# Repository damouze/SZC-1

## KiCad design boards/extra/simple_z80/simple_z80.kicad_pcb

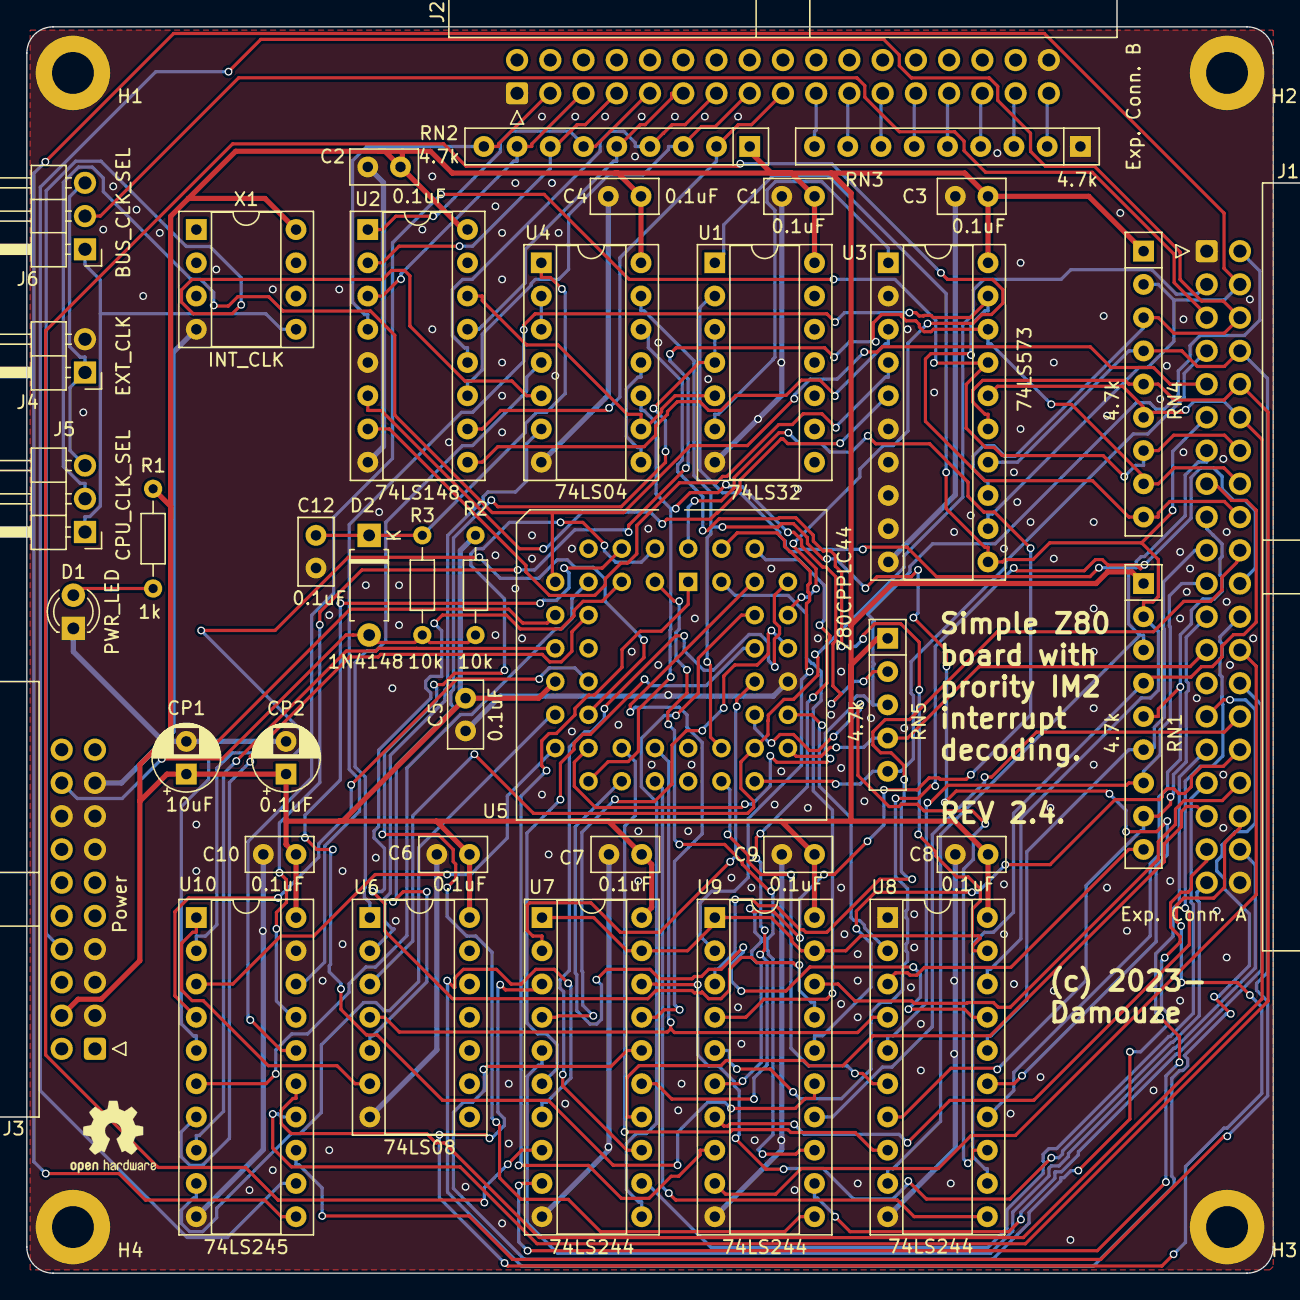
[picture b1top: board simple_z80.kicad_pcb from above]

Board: 2 copper layers, 95.2 x 95.2 mm, 44 parts (0 on the bottom side), 107 nets.

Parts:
C1, C2, C3, C4, C5, C6, C7, C8, C9, C10, C12: 0.1uF; C_Disc_D5.0mm_W2.5mm_P2.50mm
CP1: 10uF; CP_Radial_D5.0mm_P2.50mm
CP2: 0.1uF; CP_Radial_D5.0mm_P2.50mm
D1: PWR_LED; LED_D3.0mm
D2: 1N4148; D_A-405_P7.62mm_Horizontal
H1, H2, H3, H4: MountingHole_Pad; MountingHole_3.2mm_M3_ISO7380_Pad
J1: Exp. Conn. A; IDC-Header_2x20_P2.54mm_Horizontal
J2: Exp. Conn. B; IDC-Header_2x17_P2.54mm_Horizontal
J3: Power; IDC-Header_2x10_P2.54mm_Horizontal
J4: EXT_CLK; PinHeader_1x02_P2.54mm_Horizontal
J5: CPU_CLK_SEL; PinHeader_1x03_P2.54mm_Horizontal
J6: BUS_CLK_SEL; PinHeader_1x03_P2.54mm_Horizontal
R1: 1k; R_Axial_DIN0204_L3.6mm_D1.6mm_P7.62mm_Horizontal
R2, R3: 10k; R_Axial_DIN0204_L3.6mm_D1.6mm_P7.62mm_Horizontal
RN1, RN2, RN3, RN4: 4.7k; R_Array_SIP9
RN5: 4.7k; R_Array_SIP5
U1: 74LS32; DIP-14_W7.62mm_Socket
U2: 74LS148; DIP-16_W7.62mm_Socket
U3: 74LS573; DIP-20_W7.62mm_Socket
U4: 74LS04; DIP-14_W7.62mm_Socket
U5: Z80CPPLC44; PLCC-44_THT-Socket
U6: 74LS08; DIP-14_W7.62mm_Socket
U7, U8, U9: 74LS244; DIP-20_W7.62mm_Socket
U10: 74LS245; DIP-20_W7.62mm_Socket
X1: INT_CLK; DIP-8_W7.62mm_Socket

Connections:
/+5V: C1.1, C2.2, C3.1, C4.1, C5.1, C6.1, C7.1, C8.1, C9.1, C10.1, CP1.1, CP2.1, J3.4, R1.1, R2.1, RN1.1 (common), RN2.1 (common), RN4.1 (common), RN5.1 (common), U1.14 (VCC), U2.16 (VCC), U3.20 (VCC), U4.14 (VCC), U5.13 (VCC), U6.14 (VCC), U7.20 (VCC), U8.20 (VCC), U9.20 (VCC), U10.20 (VCC), X1.8 (Vcc)
/BUS_CLK: J1.5, J6.2
/B_A0: J1.39, U7.18 (O0a)
/B_A1: J1.37, U7.16 (O1a)
/B_A2: J1.35, U7.14 (O2a)
/B_A3: J1.33, U7.12 (O3a)
/B_A4: J1.31, U7.9 (O0b)
/B_A5: J1.29, U7.7 (O1b)
/B_A6: J1.38, U7.5 (O2b)
/B_A7: J1.36, U7.3 (O3b)
/B_A8: J1.34, U9.18 (O0a)
/B_A9: J1.32, U9.16 (O1a)
/B_A10: J1.30, U9.14 (O2a)
/B_A11: J1.28, U9.12 (O3a)
/B_A12: J1.26, U9.9 (O0b)
/B_A13: J1.24, U9.7 (O1b)
/B_A14: J1.22, U9.5 (O2b)
/B_A15: J1.20, U9.3 (O3b)
/B_D0: J1.18, RN4.9 (R8), U3.19 (Q0), U10.18 (B0)
/B_D1: J1.16, RN4.8 (R7), U3.18 (Q1), U10.17 (B1)
/B_D2: J1.14, RN4.7 (R6), U3.17 (Q2), U10.16 (B2)
/B_D3: J1.12, RN4.6 (R5), U3.16 (Q3), U10.15 (B3)
/B_D4: J1.10, RN4.5 (R4), U3.15 (Q4), U10.14 (B4)
/B_D5: J1.8, RN4.4 (R3), U3.14 (Q5), U10.13 (B5)
/B_D6: J1.6, RN4.3 (R2), U3.13 (Q6), U10.12 (B6)
/B_D7: J1.4, RN4.2 (R1), U3.12 (Q7), U10.11 (B7)
/CPU_CLK: J1.9, J5.2, U5.7 (~CLK)
/Clock & Reset circuit/EXT_CLK: J4.1, J5.3, J6.3
/Clock & Reset circuit/INT_CLK: J5.1, J6.1, X1.5 (OUT)
/Clock & Reset circuit/RESET1: U4.2, U4.3
/Clock & Reset circuit/~PWR_OK: U4.6, U6.2
/Clock & Reset circuit/~RESET1: U4.4, U6.1
/GND: C1.2, C2.1, C3.2, C4.2, C5.2, C6.2, C7.2, C8.2, C9.2, C10.2, C12.2, CP1.2, CP2.2, D1.1 (K), H1.1, H2.1, H3.1, H4.1, J1.1, J1.40, J2.1, J2.34, J3.3, J3.5, J3.7, J3.13, J3.15, J3.16, J3.17, J4.2, RN3.1 (common), U1.7 (GND), U2.5 (EI), U2.8 (GND), U3.2 (D0), U3.6 (D4), U3.7 (D5), U3.8 (D6), U3.9 (D7), U3.10 (GND), U4.7 (GND), U5.33 (GND), U6.7 (GND), U7.10 (GND), U8.1 (OEa), U8.10 (GND), U9.10 (GND), U10.10 (GND), U10.19 (CE), X1.4 (GND)
/MCU/A0: U5.34 (A0), U7.2 (I0a)
/MCU/A1: U5.35 (A1), U7.4 (I1a)
/MCU/A2: U5.36 (A2), U7.6 (I2a)
/MCU/A3: U5.37 (A3), U7.8 (I3a)
/MCU/A4: U5.38 (A4), U7.11 (I0b)
/MCU/A5: U5.39 (A5), U7.13 (I1b)
/MCU/A6: U5.40 (A6), U7.15 (I2b)
/MCU/A7: U5.41 (A7), U7.17 (I3b)
/MCU/A8: U5.42 (A8), U9.2 (I0a)
/MCU/A9: U5.43 (A9), U9.4 (I1a)
/MCU/A10: U5.44 (A10), U9.6 (I2a)
/MCU/A11: U5.1 (A11), U9.8 (I3a)
/MCU/A12: U5.2 (A12), U9.11 (I0b)
/MCU/A13: U5.3 (A13), U9.13 (I1b)
/MCU/A14: U5.4 (A14), U9.15 (I2b)
/MCU/A15: U5.5 (A15), U9.17 (I3b)
/MCU/BUSACK: U4.12, U7.1 (OEa), U7.19 (OEb), U8.19 (OEb), U9.1 (OEa), U9.19 (OEb)
/MCU/D0: U5.16 (D0), U10.2 (A0)
/MCU/D1: U5.17 (D1), U10.3 (A1)
/MCU/D2: U5.14 (D2), U10.4 (A2)
/MCU/D3: U5.9 (D3), U10.5 (A3)
/MCU/D4: U5.8 (D4), U10.6 (A4)
/MCU/D5: U5.10 (D5), U10.7 (A5)
/MCU/D6: U5.11 (D6), U10.8 (A6)
/MCU/D7: U5.15 (D7), U10.9 (A7)
/MCU/~BUSACK: U4.13, U5.27 (~BUSACK), U8.15 (I2b)
/MCU/~HALT: U5.20 (~HALT), U8.17 (I3b)
/MCU/~IORQ: U5.22 (~IORQ), U8.11 (I0b)
/MCU/~M1: U5.31 (~M1), U8.2 (I0a)
/MCU/~MREQ: U5.21 (~MREQ), U8.8 (I3a)
/MCU/~RD: U5.23 (~RD), U6.4, U8.4 (I1a)
/MCU/~RFSH: U5.32 (~RFSH), U8.13 (I1b)
/MCU/~WR: U5.26 (~WR), U8.6 (I2a)
/M_A14: J2.33, RN3.2 (R1)
/M_A15: J2.31, RN3.3 (R2)
/M_A16: J2.29, RN3.4 (R3)
/M_A17: J2.27, RN3.5 (R4)
/M_A18: J2.25, RN3.6 (R5)
/M_A19: J2.23, RN3.7 (R6)
/M_A20: J2.21, RN3.8 (R7)
/M_A21: J2.19, RN3.9 (R8)
/PWR_OK: J3.8, U4.5
/~BUSREQ: J1.25, RN5.4 (R3), U5.29 (~BUSRQ)
/~B_BUSACK: J1.21, RN1.7 (R6), U8.5 (O2b)
/~B_HALT: RN1.9 (R8), U8.3 (O3b)
/~B_IORQ: J1.13, RN1.3 (R2), U1.2, U8.9 (O0b)
/~B_M1: J1.11, RN1.2 (R1), U1.1, U3.11 (Load), U8.18 (O0a)
/~B_MREQ: J1.15, RN1.4 (R3), U8.12 (O3a)
/~B_RD: J1.19, RN1.6 (R5), U8.16 (O1a)
/~B_RFSH: J1.23, RN1.8 (R7), U8.7 (O1b)
/~B_WR: J1.17, RN1.5 (R4), U8.14 (O2a)
/~CPU_INT: RN5.2 (R1), U4.10, U5.18 (~INT)
/~IM2_INT: U1.5, U2.14 (GS), U4.9
/~INT0: J2.17, RN2.2 (R1), U2.10 (IO)
/~INT1: J2.15, RN2.3 (R2), U2.11 (I1)
/~INT2: J2.13, RN2.4 (R3), U2.12 (I2)
/~INT3: J2.11, RN2.5 (R4), U2.13 (I3)
/~INT4: J2.9, RN2.6 (R5), U2.1 (I4)
/~INT5: J2.7, RN2.7 (R6), U2.2 (I5)
/~INT6: J2.5, RN2.8 (R7), U2.3 (I6)
/~INT7: J2.3, RN2.9 (R8), U2.4 (I7)
/~INTA: U1.3, U1.4, U6.5
/~NMI: J1.2, RN5.3 (R2), U5.19 (~NMI)
/~RESET_SW: D2.2 (A), J3.18, R2.2, R3.2
/~RESET: J1.3, U5.30 (~RESET), U6.3
/~WAIT: J1.7, RN5.5 (R4), U5.28 (~WAIT)
unnamed: D1.2 (A), R1.2
unnamed: C12.1, D2.1 (K), R3.1, U4.1
unnamed: U2.9 (S0), U3.3 (D1)
unnamed: U2.7 (S1), U3.4 (D2)
unnamed: U2.6 (S2), U3.5 (D3)
unnamed: U1.6, U3.1 (OE)
unnamed: U4.8, U4.11
unnamed: U6.6, U10.1 (A->B)

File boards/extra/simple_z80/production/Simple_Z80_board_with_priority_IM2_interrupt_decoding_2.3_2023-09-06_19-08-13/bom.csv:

Designator,Footprint,Quantity,Value,LCSC Part #
"C1, C10, C12, C2, C3, C4, C5, C6, C7, C8, C9",C_Disc_D5.0mm_W2.5mm_P2.50mm,11,0.1uF,
CP1,CP_Radial_D5.0mm_P2.50mm,1,10uF,
CP2,CP_Radial_D5.0mm_P2.50mm,1,0.1uF,
D1,LED_D3.0mm,1,PWR_LED,
D2,D_A-405_P7.62mm_Horizontal,1,D,
"H1, H2, H3, H4",MountingHole_3.2mm_M3_ISO7380_Pad,4,MountingHole_Pad,
J1,IDC-Header_2x20_P2.54mm_Horizontal,1,Exp. Conn. A,
J2,IDC-Header_2x17_P2.54mm_Horizontal,1,Exp. Conn. B,
J3,IDC-Header_2x10_P2.54mm_Horizontal,1,Power,
J4,PinHeader_1x02_P2.54mm_Horizontal,1,EXT_CLK,
J5,PinHeader_1x03_P2.54mm_Horizontal,1,CPU_CLK_SEL,
J6,PinHeader_1x03_P2.54mm_Horizontal,1,BUS_CLK_SEL,
R1,R_Axial_DIN0204_L3.6mm_D1.6mm_P7.62mm_Horizontal,1,470,
"R2, R3",R_Axial_DIN0204_L3.6mm_D1.6mm_P7.62mm_Horizontal,2,10k,
"RN1, RN2, RN3, RN4",R_Array_SIP9,4,4.7k,
RN5,R_Array_SIP5,1,4.7k,
U1,DIP-14_W7.62mm_Socket,1,74LS32,
U10,DIP-20_W7.62mm_Socket,1,74LS245,
U2,DIP-16_W7.62mm_Socket,1,74LS148,
U3,DIP-20_W7.62mm_Socket,1,74LS573,
U4,DIP-14_W7.62mm_Socket,1,74LS04,
U5,PLCC-44_THT-Socket,1,Z80CPPLC44,
U6,DIP-14_W7.62mm_Socket,1,74LS08,
"U7, U8, U9",DIP-20_W7.62mm_Socket,3,74LS244,
X1,DIP-8_W7.62mm_Socket,1,INT_CLK,

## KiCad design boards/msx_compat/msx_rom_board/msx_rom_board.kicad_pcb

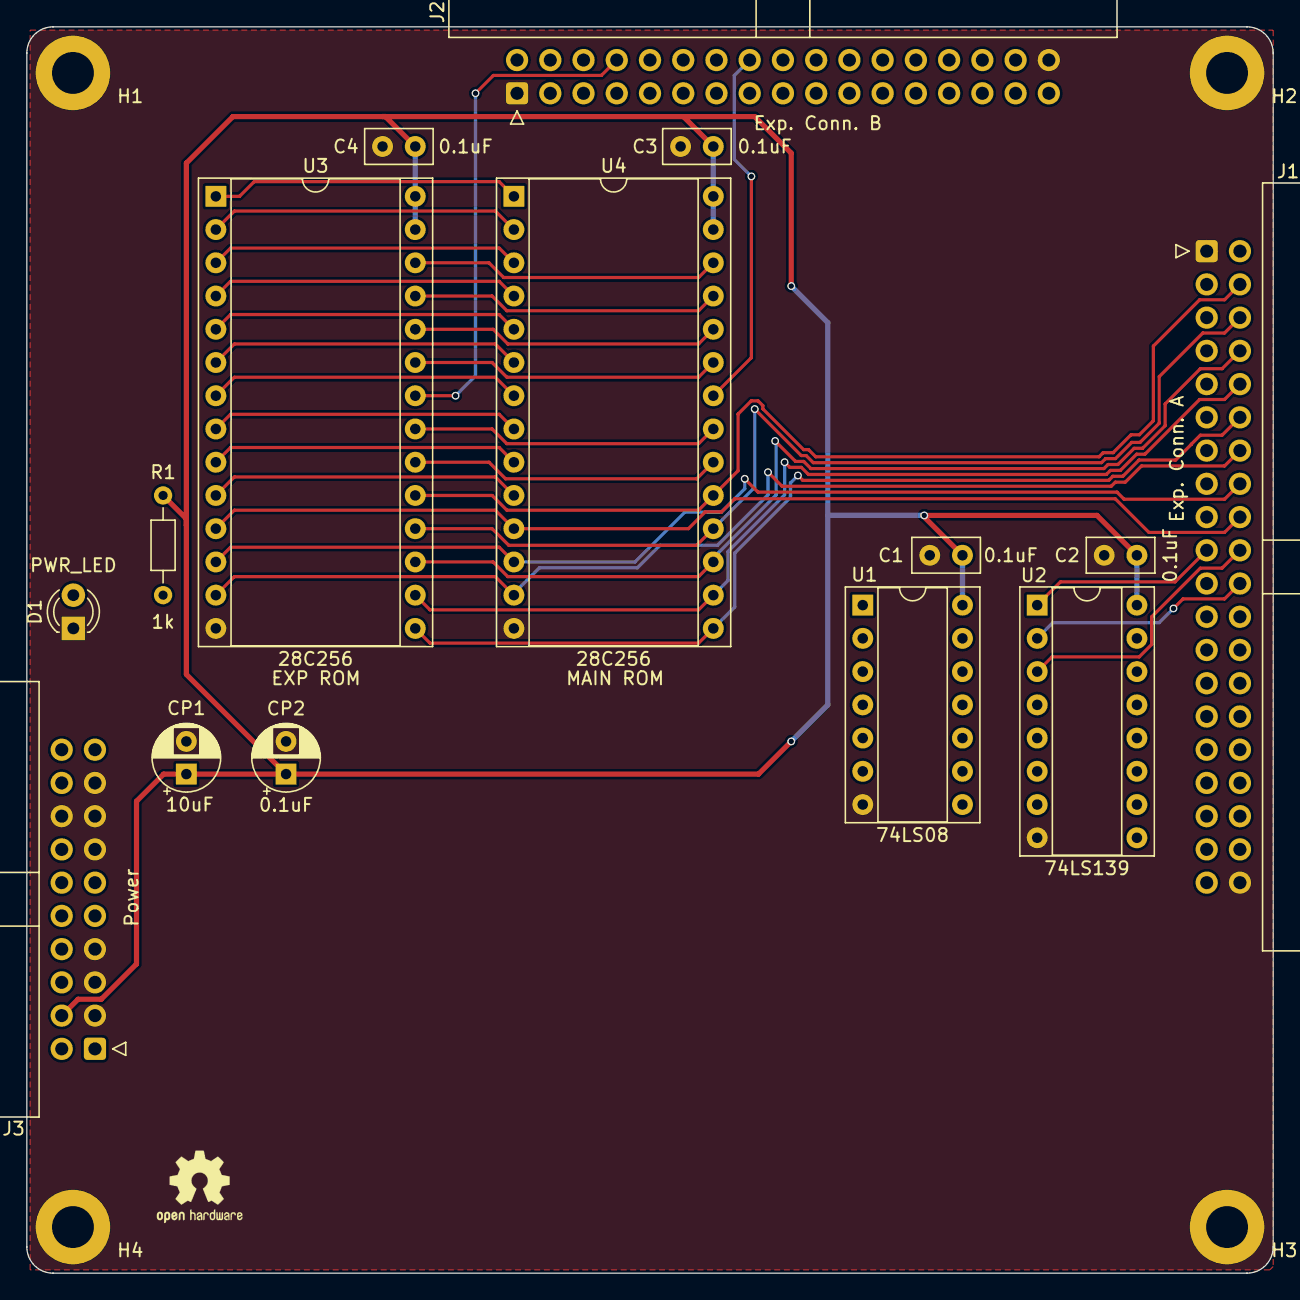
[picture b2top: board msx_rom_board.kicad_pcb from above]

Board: 2 copper layers, 95.2 x 95.2 mm, 19 parts (0 on the bottom side), 33 nets.

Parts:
C1, C2, C3, C4: 0.1uF; C_Disc_D5.0mm_W2.5mm_P2.50mm
CP1: 10uF; CP_Radial_D5.0mm_P2.50mm
CP2: 0.1uF; CP_Radial_D5.0mm_P2.50mm
D1: PWR_LED; LED_D3.0mm
H1, H2, H3, H4: MountingHole_Pad; MountingHole_3.2mm_M3_ISO7380_Pad
J1: Exp. Conn. A; IDC-Header_2x20_P2.54mm_Horizontal
J2: Exp. Conn. B; IDC-Header_2x17_P2.54mm_Horizontal
J3: Power; IDC-Header_2x10_P2.54mm_Horizontal
R1: 1k; R_Axial_DIN0204_L3.6mm_D1.6mm_P7.62mm_Horizontal
U1: 74LS08; DIP-14_W7.62mm_Socket
U2: 74LS139; DIP-16_W7.62mm_Socket
U3, U4: 28C256; DIP-28_W15.24mm_Socket

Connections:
/+5V: C1.1, C2.1, C3.1, C4.1, CP1.1, CP2.1, J3.4, R1.1, U1.14 (VCC), U2.16 (VCC), U3.27 (~WE), U3.28 (VCC), U4.27 (~WE), U4.28 (VCC)
/B_A0: J1.39, U3.10 (A0), U4.10 (A0)
/B_A1: J1.37, U3.9 (A1), U4.9 (A1)
/B_A2: J1.35, U3.8 (A2), U4.8 (A2)
/B_A3: J1.33, U3.7 (A3), U4.7 (A3)
/B_A4: J1.31, U3.6 (A4), U4.6 (A4)
/B_A5: J1.29, U3.5 (A5), U4.5 (A5)
/B_A6: J1.38, U3.4 (A6), U4.4 (A6)
/B_A7: J1.36, U3.3 (A7), U4.3 (A7)
/B_A8: J1.34, U3.25 (A8), U4.25 (A8)
/B_A9: J1.32, U3.24 (A9), U4.24 (A9)
/B_A10: J1.30, U3.21 (A10), U4.21 (A10)
/B_A11: J1.28, U3.23 (A11), U4.23 (A11)
/B_A12: J1.26, U3.2 (A12), U4.2 (A12)
/B_A13: J1.24, U3.26 (A13), U4.26 (A13)
/B_A14: J1.22, U2.2 (A0), U3.1 (A14), U4.1 (A14)
/B_A15: J1.20, U2.3 (A1)
/B_D0: J1.18, U3.11 (D0), U4.11 (D0)
/B_D1: J1.16, U3.12 (D1), U4.12 (D1)
/B_D2: J1.14, U3.13 (D2), U4.13 (D2)
/B_D3: J1.12, U3.15 (D3), U4.15 (D3)
/B_D4: J1.10, U3.16 (D4), U4.16 (D4)
/B_D5: J1.8, U3.17 (D5), U4.17 (D5)
/B_D6: J1.6, U3.18 (D6), U4.18 (D6)
/B_D7: J1.4, U3.19 (D7), U4.19 (D7)
/GND: C1.2, C2.2, C3.2, C4.2, CP1.2, CP2.2, D1.1 (K), H1.1, H2.1, H3.1, H4.1, J1.1, J1.40, J2.1, J2.34, J3.3, J3.5, J3.7, J3.13, J3.15, J3.16, J3.17, U1.7 (GND), U2.8 (GND), U3.14 (GND), U4.14 (GND)
/~B_RD: J1.19, U2.1 (E)
/~ROMHI_CS: U1.5, U2.5 (O1)
/~ROMLO_CS: U1.4, U2.4 (O0)
/~ROM_CS: U1.6, U3.20 (~CS), U4.20 (~CS)
/~SBSLTSL30: J2.16, U4.22 (~OE)
/~SLTSL0: J2.8, U3.22 (~OE)
unnamed: D1.2 (A), R1.2

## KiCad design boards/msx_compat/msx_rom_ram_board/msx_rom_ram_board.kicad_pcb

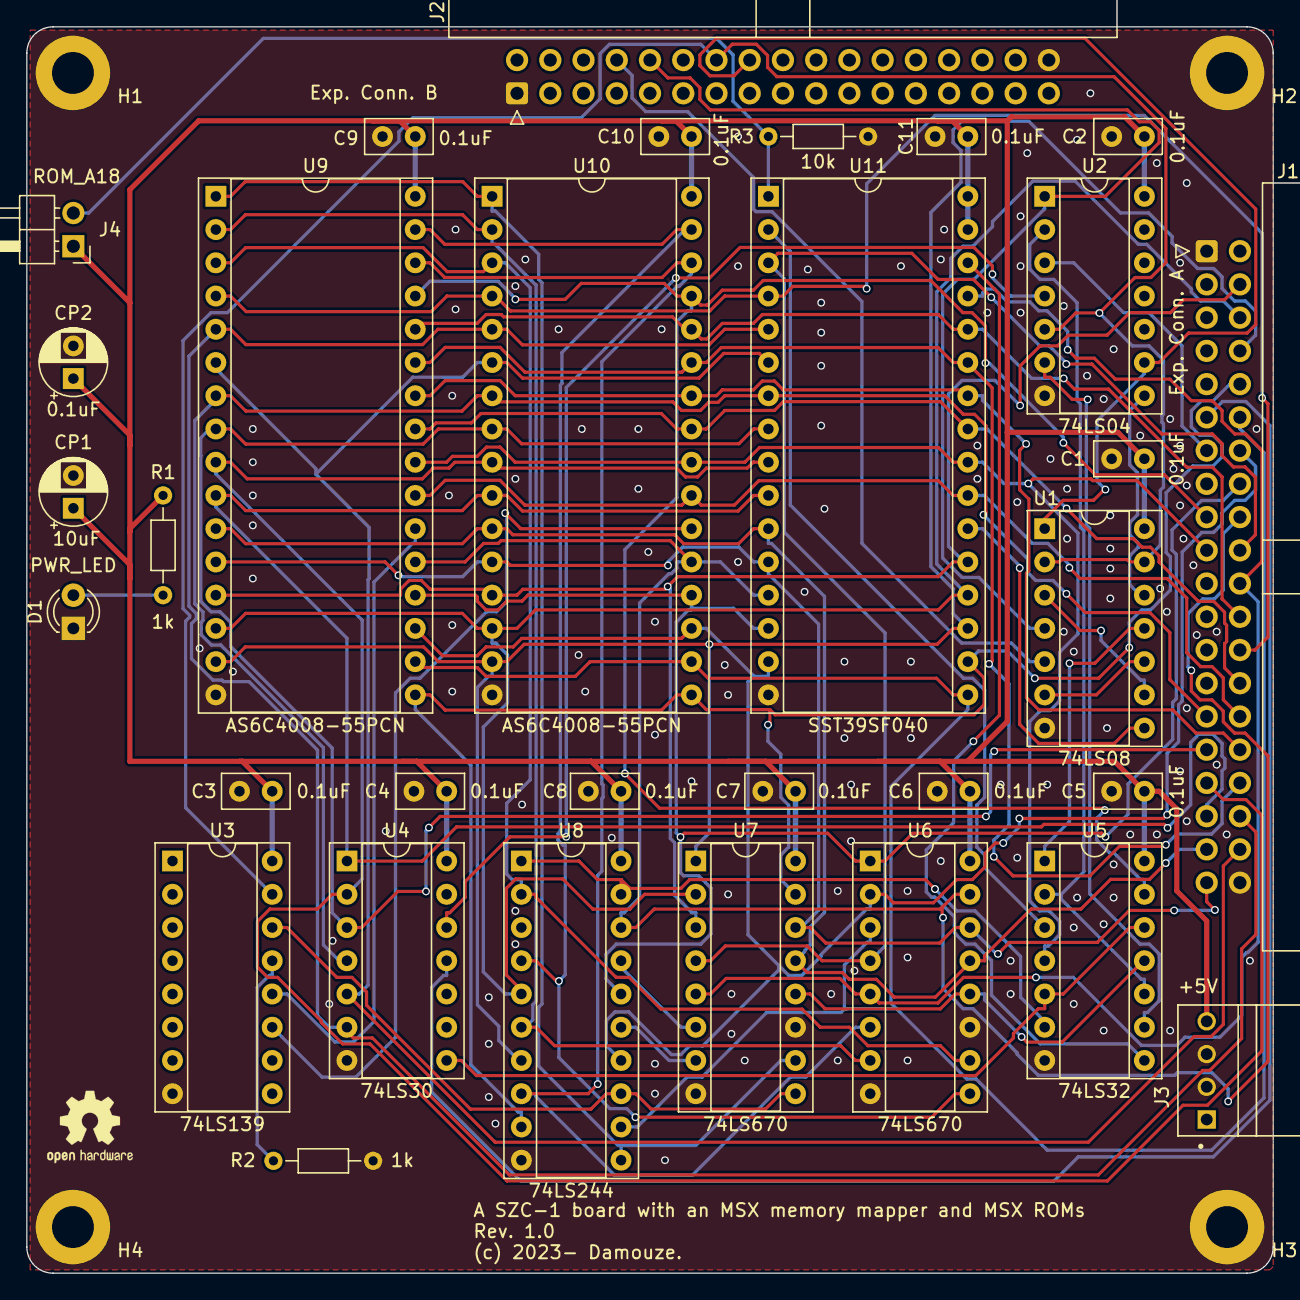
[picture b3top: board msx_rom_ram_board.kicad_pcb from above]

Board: 2 copper layers, 95.2 x 95.2 mm, 36 parts (0 on the bottom side), 60 nets.

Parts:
C1, C2, C3, C4, C5, C6, C7, C8, C9, C10, C11: 0.1uF; C_Disc_D5.0mm_W2.5mm_P2.50mm
CP1: 10uF; CP_Radial_D5.0mm_P2.50mm
CP2: 0.1uF; CP_Radial_D5.0mm_P2.50mm
D1: PWR_LED; LED_D3.0mm
H1, H2, H3, H4: MountingHole_Pad; MountingHole_3.2mm_M3_ISO7380_Pad
J1: Exp. Conn. A; IDC-Header_2x20_P2.54mm_Horizontal
J2: Exp. Conn. B; IDC-Header_2x17_P2.54mm_Horizontal
J3: Power; TE_171826-4
J4: ROM_A18; PinHeader_1x02_P2.54mm_Horizontal
R1, R2: 1k; R_Axial_DIN0204_L3.6mm_D1.6mm_P7.62mm_Horizontal
R3: 10k; R_Axial_DIN0204_L3.6mm_D1.6mm_P7.62mm_Horizontal
U1: 74LS08; DIP-14_W7.62mm_Socket
U2: 74LS04; DIP-14_W7.62mm_Socket
U3: 74LS139; DIP-16_W7.62mm_Socket
U4: 74LS30; DIP-14_W7.62mm_Socket
U5: 74LS32; DIP-14_W7.62mm_Socket
U6, U7: 74LS670; DIP-16_W7.62mm_Socket
U8: 74LS244; DIP-20_W7.62mm_Socket
U9, U10: AS6C4008-55PCN; DIP-32_W15.24mm_Socket
U11: SST39SF040; DIP-32_W15.24mm_Socket

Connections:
/+5V: C1.1, C2.1, C3.1, C4.1, C5.1, C6.1, C7.1, C8.1, C9.1, C10.1, C11.1, CP1.1, CP2.1, J3.4, J4.1, R1.1, U1.14 (VCC), U2.14 (VCC), U3.16 (VCC), U4.14 (VCC), U5.14 (VCC), U6.16 (VCC), U7.16 (VCC), U8.20 (VCC), U9.32 (VCC), U10.32 (VCC), U11.31 (PGM), U11.32 (VCC)
/B_A0: J1.39, U6.14 (Wa), U7.14 (Wa), U9.12 (A0), U10.12 (A0), U11.12 (A0)
/B_A1: J1.37, U6.13 (Wb), U7.13 (Wb), U9.11 (A1), U10.11 (A1), U11.11 (A1)
/B_A2: J1.35, U4.1, U9.10 (A2), U10.10 (A2), U11.10 (A2)
/B_A3: J1.33, U4.2, U9.9 (A3), U10.9 (A3), U11.9 (A3)
/B_A4: J1.31, U4.3, U9.8 (A4), U10.8 (A4), U11.8 (A4)
/B_A5: J1.29, U4.4, U9.7 (A5), U10.7 (A5), U11.7 (A5)
/B_A6: J1.38, U4.5, U9.6 (A6), U10.6 (A6), U11.6 (A6)
/B_A7: J1.36, U4.6, U9.5 (A7), U10.5 (A7), U11.5 (A7)
/B_A8: J1.34, U9.27 (A8), U10.27 (A8), U11.27 (A8)
/B_A9: J1.32, U9.26 (A9), U10.26 (A9), U11.26 (A9)
/B_A10: J1.30, U9.23 (A10), U10.23 (A10), U11.23 (A10)
/B_A11: J1.28, U9.25 (A11), U10.25 (A11), U11.25 (A11)
/B_A12: J1.26, U9.4 (A12), U10.4 (A12), U11.4 (A12)
/B_A13: J1.24, U9.28 (A13), U10.28 (A13), U11.28 (A13)
/B_A14: J1.22, U6.5 (Ra), U7.5 (Ra), U11.29 (A14)
/B_A15: J1.20, U6.4 (Rb), U7.4 (Rb), U11.3 (A15)
/B_D0: J1.18, U6.15 (D1), U8.18 (O0a), U9.21 (DQ7), U10.21 (DQ7), U11.13 (D0)
/B_D1: J1.16, U6.1 (D2), U8.16 (O1a), U9.20 (DQ6), U10.20 (DQ6), U11.14 (D1)
/B_D2: J1.14, U6.2 (D3), U8.14 (O2a), U9.19 (DQ5), U10.19 (DQ5), U11.15 (D2)
/B_D3: J1.12, U6.3 (D4), U8.12 (O3a), U9.18 (DQ4), U10.18 (DQ4), U11.17 (D3)
/B_D4: J1.10, U7.15 (D1), U8.9 (O0b), U9.17 (DQ3), U10.17 (DQ3), U11.18 (D4)
/B_D5: J1.8, U7.1 (D2), U8.7 (O1b), U9.15 (DQ2), U10.15 (DQ2), U11.19 (D5)
/B_D6: J1.6, U7.2 (D3), U8.5 (O2b), U9.14 (DQ1), U10.14 (DQ1), U11.20 (D6)
/B_D7: J1.4, U7.3 (D4), U9.13 (DQ0), U10.13 (DQ0), U11.21 (D7)
/GND: C1.2, C2.2, C3.2, C4.2, C5.2, C6.2, C7.2, C8.2, C9.2, C10.2, C11.2, CP1.2, CP2.2, D1.1 (K), H1.1, H2.1, H3.1, H4.1, J1.1, J1.40, J2.1, J2.34, J3.2, J3.3, R2.2, R3.2, U1.7 (GND), U2.7 (GND), U3.8 (GND), U4.7 (GND), U5.7 (GND), U6.8 (GND), U6.11 (~Er), U7.8 (GND), U7.11 (~Er), U8.10 (GND), U9.16 (VSS), U10.16 (VSS), U11.16 (GND)
/G_A20: R2.1, U3.13 (A1)
/IORQ: U2.4, U4.12
/ROM_A16: U5.3, U11.2 (A16)
/ROM_A17: U5.8, U11.30 (A17)
/ROM_A18: J4.2, R3.1, U11.1 (A18)
/R_A14: U6.10 (Q1), U8.2 (I0a), U9.3 (A14), U10.3 (A14)
/R_A15: U6.9 (Q2), U8.4 (I1a), U9.31 (A15), U10.31 (A15)
/R_A16: U6.7 (Q3), U8.6 (I2a), U9.2 (A16), U10.2 (A16)
/R_A17: U6.6 (Q4), U8.8 (I3a), U9.30 (A17), U10.30 (A17)
/R_A18: U7.10 (Q1), U8.11 (I0b), U9.1 (A18), U10.1 (A18)
/R_A19: U3.14 (A0), U7.9 (Q2), U8.13 (I1b)
/R_A20: U7.7 (Q3), U8.15 (I2b)
/R_A21: U7.6 (Q4), U8.17 (I3b)
/~B_IORQ: J1.13, U2.3
/~B_M1: J1.11, U4.11
/~B_RD: J1.19, U5.4, U9.24 (OE#), U10.24 (OE#), U11.24 (OE)
/~B_WR: J1.17, U5.13, U9.29 (WE#), U10.29 (WE#)
/~IO_RD: U5.6, U8.1 (OEa), U8.19 (OEb)
/~IO_WR: U5.11, U6.12 (~Ew), U7.12 (~Ew)
/~RAM0_CS: U3.12 (O0), U9.22 (CE#)
/~RAM1_CS: U3.11 (O1), U10.22 (CE#)
/~ROM_CS: U1.8, U11.22 (CE)
/~SBSLTSL30: J2.16, U1.1, U2.9
/~SBSLTSL31: J2.14, U1.2, U1.13, U2.5, U3.15 (E)
/~SBSLTSL33: J2.10, U1.4, U2.1
/~SLTSL0: J2.8, U1.5
unnamed: D1.2 (A), R1.2
unnamed: U1.3, U1.9
unnamed: U1.6, U1.10
unnamed: U1.11, U5.1
unnamed: U1.12, U2.8
unnamed: U2.2, U5.2, U5.10
unnamed: U2.6, U5.9
unnamed: U4.8, U5.5, U5.12

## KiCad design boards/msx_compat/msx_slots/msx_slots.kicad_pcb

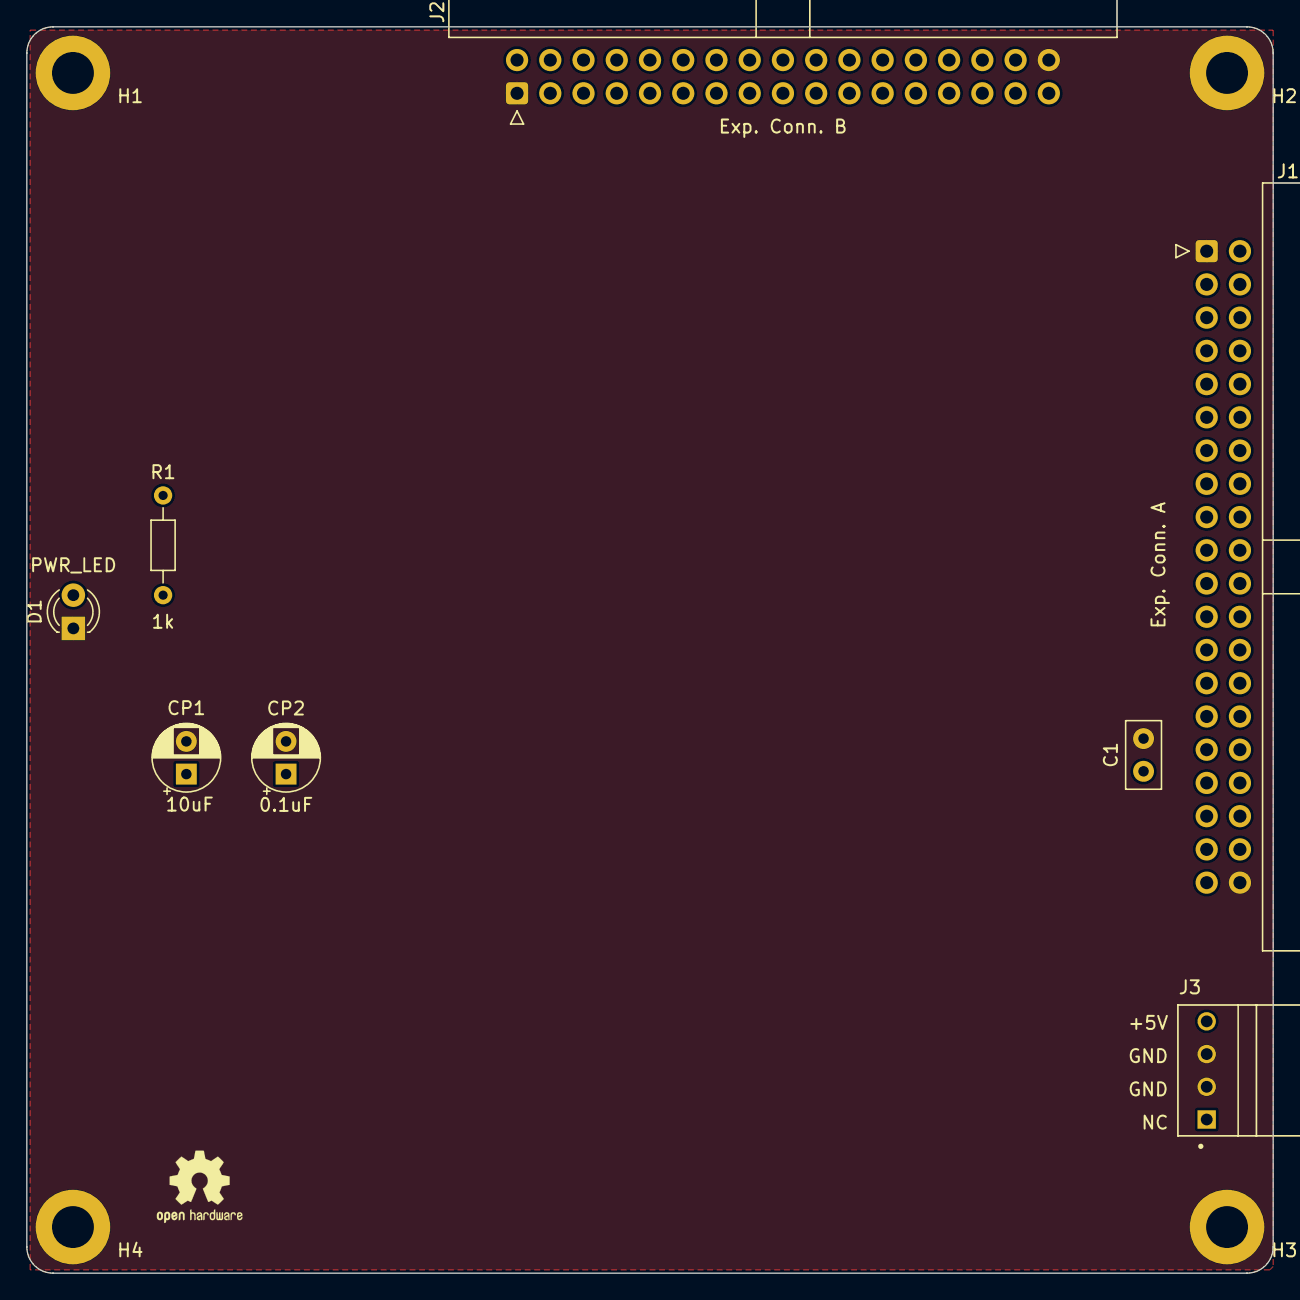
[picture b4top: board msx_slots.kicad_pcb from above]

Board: 2 copper layers, 95.2 x 95.2 mm, 12 parts (0 on the bottom side), 3 nets, no tracks yet.

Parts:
C1: 0.1uF; C_Disc_D5.0mm_W2.5mm_P2.50mm
CP1: 10uF; CP_Radial_D5.0mm_P2.50mm
CP2: 0.1uF; CP_Radial_D5.0mm_P2.50mm
D1: PWR_LED; LED_D3.0mm
H1, H2, H3, H4: MountingHole_Pad; MountingHole_3.2mm_M3_ISO7380_Pad
J1: Exp. Conn. A; IDC-Header_2x20_P2.54mm_Horizontal
J2: Exp. Conn. B; IDC-Header_2x17_P2.54mm_Horizontal
J3: Power; TE_171826-4
R1: 1k; R_Axial_DIN0204_L3.6mm_D1.6mm_P7.62mm_Horizontal

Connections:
/+5V: C1.1, CP1.1, CP2.1, J3.4, R1.1
/GND: C1.2, CP1.2, CP2.2, D1.1 (K), H1.1, H2.1, H3.1, H4.1, J1.1, J1.40, J2.1, J2.34, J3.2, J3.3
unnamed: D1.2 (A), R1.2

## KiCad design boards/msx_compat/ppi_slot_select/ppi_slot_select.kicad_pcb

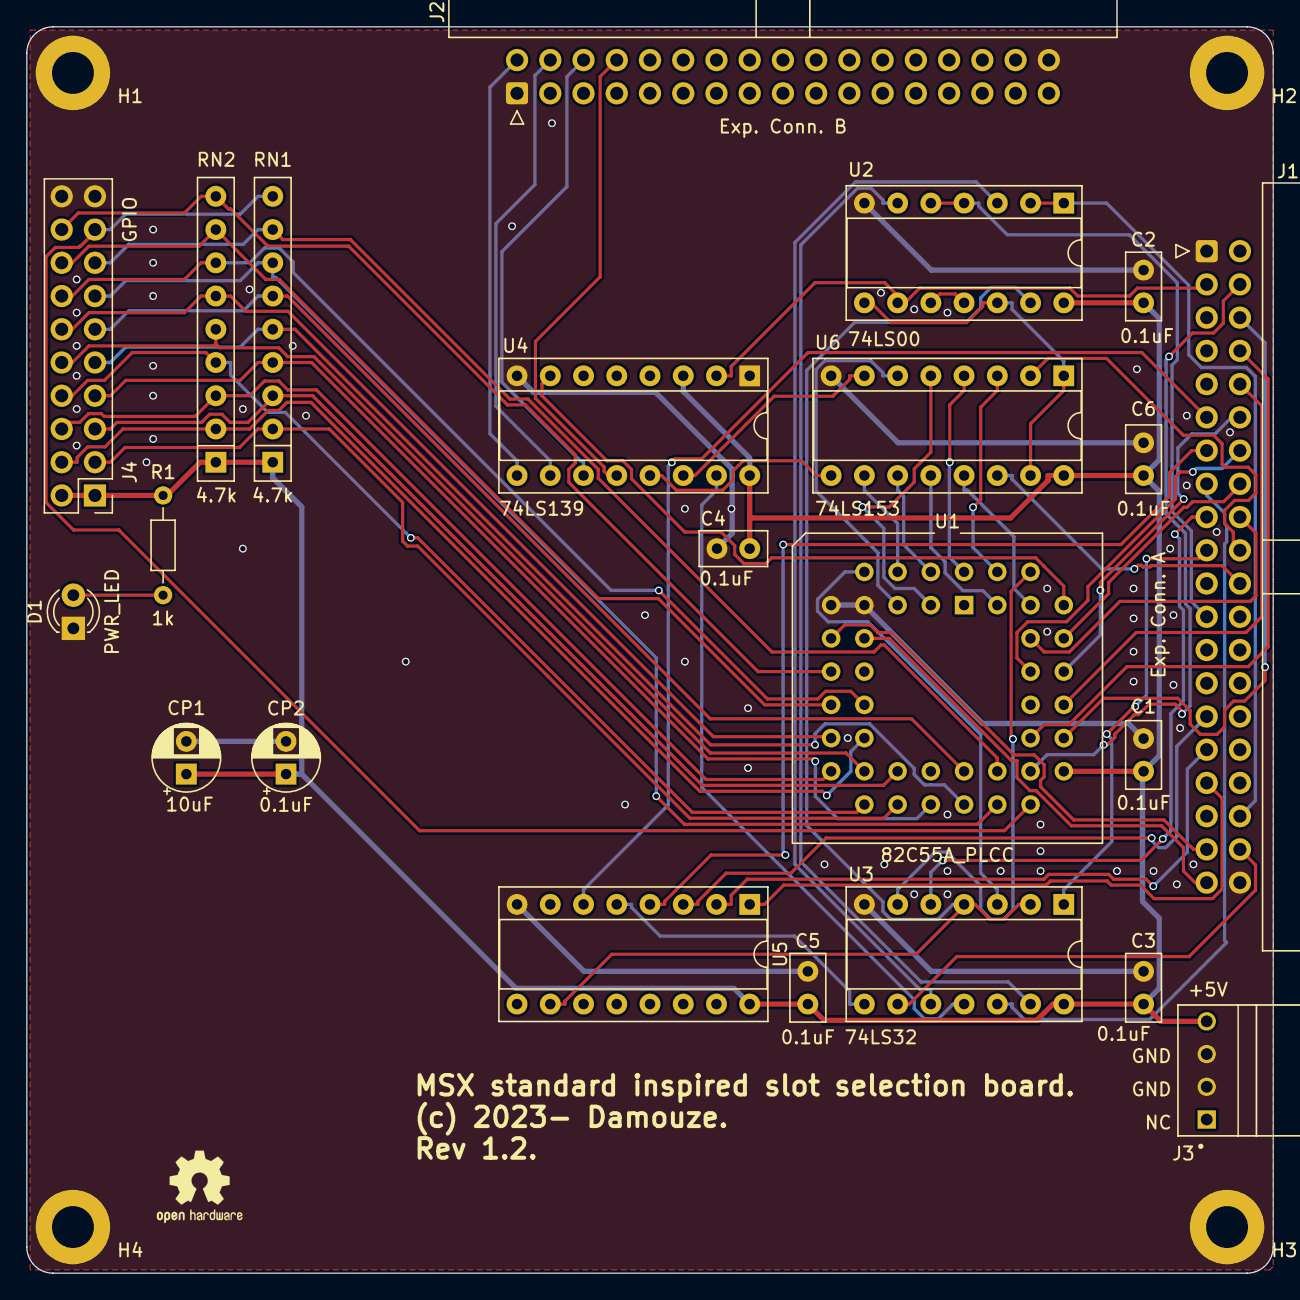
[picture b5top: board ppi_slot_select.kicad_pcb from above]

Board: 2 copper layers, 95.2 x 95.2 mm, 26 parts (0 on the bottom side), 67 nets.

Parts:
C1, C2, C3, C4, C5, C6: 0.1uF; C_Disc_D5.0mm_W2.5mm_P2.50mm
CP1: 10uF; CP_Radial_D5.0mm_P2.50mm
CP2: 0.1uF; CP_Radial_D5.0mm_P2.50mm
D1: PWR_LED; LED_D3.0mm
H1, H2, H3, H4: MountingHole_Pad; MountingHole_3.2mm_M3_ISO7380_Pad
J1: Exp. Conn. A; IDC-Header_2x20_P2.54mm_Horizontal
J2: Exp. Conn. B; IDC-Header_2x17_P2.54mm_Horizontal
J3: Power; TE_171826-4
J4: GPIO; PinHeader_2x10_P2.54mm_Vertical
R1: 1k; R_Axial_DIN0204_L3.6mm_D1.6mm_P7.62mm_Horizontal
RN1, RN2: 4.7k; R_Array_SIP9
U1: 82C55A_PLCC; PLCC-44_THT-Socket
U2: 74LS00; DIP-14_W7.62mm_Socket
U3: 74LS32; DIP-14_W7.62mm_Socket
U4: 74LS139; DIP-16_W7.62mm_Socket
U5: 74LS138; DIP-16_W7.62mm_Socket
U6: 74LS153; DIP-16_W7.62mm_Socket

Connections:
/+5V: C1.1, C2.1, C3.1, C4.1, C5.1, C6.1, CP1.1, CP2.1, J3.4, J4.1, J4.2, R1.1, RN1.1 (common), RN2.1 (common), U1.29 (VCC), U2.14 (VCC), U3.14 (VCC), U4.3 (A1), U4.16 (VCC), U5.16 (VCC), U6.16 (VCC)
/B_A0: J1.39, U1.10 (A0)
/B_A1: J1.37, U1.9 (A1)
/B_A3: J1.33, U5.1 (A0)
/B_A4: J1.31, U5.2 (A1)
/B_A5: J1.29, U5.3 (A2)
/B_A6: J1.38, U3.9
/B_A7: J1.36, U2.1, U2.2
/B_A14: J1.22, U6.14 (S0)
/B_A15: J1.20, U6.2 (S1)
/B_D0: J1.18, U1.38 (D0)
/B_D1: J1.16, U1.37 (D1)
/B_D2: J1.14, U1.36 (D2)
/B_D3: J1.12, U1.35 (D3)
/B_D4: J1.10, U1.33 (D4)
/B_D5: J1.8, U1.32 (D5)
/B_D6: J1.6, U1.31 (D6)
/B_D7: J1.4, U1.30 (D7)
/GND: C1.2, C2.2, C3.2, C4.2, C5.2, C6.2, CP1.2, CP2.2, D1.1 (K), H1.1, H2.1, H3.1, H4.1, J1.1, J1.40, J2.1, J2.34, J3.2, J3.3, J4.19, J4.20, U1.7 (~CS), U1.8 (GND), U2.7 (GND), U3.7 (GND), U4.1 (E), U4.8 (GND), U5.8 (GND), U6.8 (GND)
/PB0: J4.3, RN1.2 (R1), U1.20 (PB0)
/PB1: J4.5, RN1.3 (R2), U1.21 (PB1)
/PB2: J4.7, RN1.4 (R3), U1.22 (PB2)
/PB3: J4.9, RN1.5 (R4), U1.24 (PB3)
/PB4: J4.11, RN1.6 (R5), U1.25 (PB4)
/PB5: J4.13, RN1.7 (R6), U1.26 (PB5)
/PB6: J4.15, RN1.8 (R7), U1.27 (PB6)
/PB7: J4.17, RN1.9 (R8), U1.28 (PB7)
/PC0: J4.4, RN2.2 (R1), U1.16 (PC0)
/PC1: J4.6, RN2.3 (R2), U1.17 (PC1)
/PC2: J4.8, RN2.4 (R3), U1.18 (PC2)
/PC3: J4.10, RN2.5 (R4), U1.19 (PC3)
/PC4: J4.12, RN2.6 (R5), U1.15 (PC4)
/PC5: J4.14, RN2.7 (R6), U1.14 (PC5)
/PC6: J4.16, RN2.8 (R7), U1.13 (PC6)
/PC7: J4.18, RN2.9 (R8), U1.11 (PC7)
/RESET: U1.39 (RESET), U4.7 (O3)
/Y5: U2.13, U3.2, U3.4, U5.10 (O5)
/~B_IORQ: J1.13, U5.4 (E1)
/~B_M1: J1.11, U5.6 (E3)
/~B_MREQ: J1.15, U3.12
/~B_RD: J1.19, U3.1
/~B_RFSH: J1.23, U2.4, U2.5
/~B_WR: J1.17, U3.5
/~CS0H: U1.4 (PA1), U6.10 (I0b)
/~CS0L: U1.5 (PA0), U6.6 (I0a)
/~CS1H: U1.2 (PA3), U6.11 (I1b)
/~CS1L: U1.3 (PA2), U6.5 (I1a)
/~CS2H: U1.43 (PA5), U6.12 (I2b)
/~CS2L: U1.44 (PA4), U6.4 (I2a)
/~CS3H: U1.41 (PA7), U6.13 (I3b)
/~CS3L: U1.42 (PA6), U6.3 (I3a)
/~PPI_RD: U1.6 (~RD), U3.3
/~PPI_WR: U1.40 (~WR), U3.6
/~RESET: J1.3, U2.9, U4.2 (A0)
/~SLTSL0: J2.8, U4.12 (O0)
/~SLTSL1: J2.6, U4.11 (O1)
/~SLTSL2: J2.4, U4.10 (O2)
/~SLTSL3: J2.2, U4.9 (O3)
unnamed: D1.2 (A), R1.2
unnamed: U2.3, U3.10
unnamed: U2.6, U3.13
unnamed: U2.10, U2.11
unnamed: U4.14 (A0), U6.7 (Za)
unnamed: U4.13 (A1), U6.9 (Zb)
unnamed: U3.11, U4.15 (E)
unnamed: U3.8, U5.5 (E2)
unnamed: U2.8, U2.12, U6.1 (Ea), U6.15 (Eb)

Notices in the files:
boards/extra/simple_z80/simple_z80.kicad_pcb:
(c) 2023-
boards/msx_compat/msx_rom_ram_board/msx_rom_ram_board.kicad_pcb:
(c) 2023- Damouze.
boards/msx_compat/ppi_slot_select_expanded/ppi_slot_select_expanded.kicad_pcb:
Rev ${REVISION}, (c) 2023- Damouze.
